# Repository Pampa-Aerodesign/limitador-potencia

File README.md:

# limitador-potencia

Sistema limitador de potência para motores BLDC com foco no projeto SAE Aerodesign 2024.

## Objetivo

Estamos utilizando um limitador de potência a fim de cumprir as restrições do regulamento.
Nosso GMP (conjunto motor/hélice/bateria) é capaz de consumir mais de 800 W de potência, então,
para maximizar o empuxo e a pontuação na competição, desenvolvemos este sistema.

## Como funciona

O sistema é composto por dois Arduinos Nano executando o mesmo código.
Os dois Arduinos vão fazer a leitura dos sensores de corrente e de tensão,
do sinal PWM vindo do ESC.

Após realizar as leituras, cada Arduino vai calcular um novo PWM para o motor levando em conta
a potência obtida dos sensores, de modo que a potência do motor não ultrapasse um determinado valor.

Cada Arduino também faz a leitura do PWM gerado pelo outro e verifica se o valor está dentro
de uma tolerância. Caso um dos Arduinos perceba que o PWM do outro Arduino está fora da tolerância,
seja por uma discrepância nos valores ou por uma falha no segundo Arduino,
um pino de verificação (Check) será levado ao nível lógico baixo, fazendo com que o PWM
dos Arduinos seja barrado e o PWM do receptor seja enviado ao ESC.

### Fluxograma

## Estrutura do repositório

- **limitador-potencia.ino** - Arquivo principal que inicializa o sistema;
- **params.hpp** - Arquivo que contém todas as configurações do sistema. Nele, são definidos os pinos, parâmetros, estruturas de dados e constantes;
- Pasta **src/** - Arquivos fonte contendo as funções utilizadas no arquivo principal;
- Pasta **inc/** - Arquivos cabeçalho contendo os protótipos das funções.

### Arquivos fonte

- **current.cpp** - funções relacionadas à leitura de corrente do motor;
- **voltage.cpp** - funções relacionadas à leitura de tensão da bateria;
- **pwm.cpp** - funções relacionadas à leitura dos sinais de PWM;

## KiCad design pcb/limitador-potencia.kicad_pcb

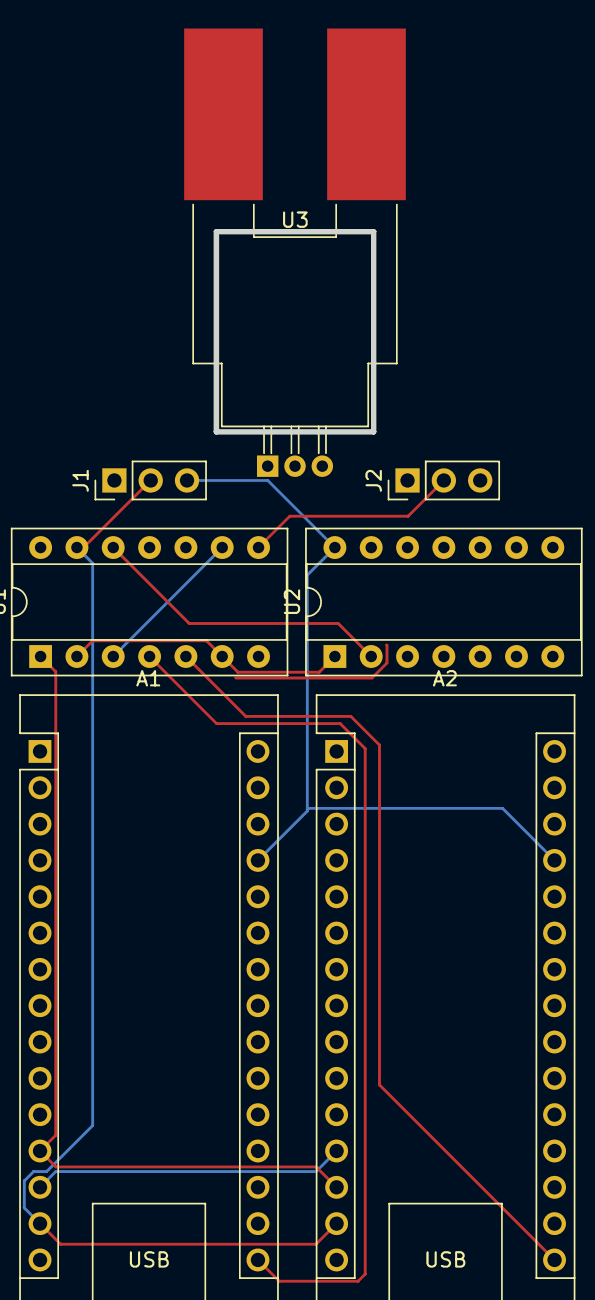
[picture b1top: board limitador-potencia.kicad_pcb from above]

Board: 2 copper layers, 7 parts (0 on the bottom side), 14 nets.

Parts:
A1, A2: Arduino_Nano_v2.x; Arduino_Nano
J1: RX Input; PinHeader_1x03_P2.54mm_Vertical
J2: ESC Output; PinHeader_1x03_P2.54mm_Vertical
U1: 74HC00; CERDIP-14_W7.62mm_SideBrazed_Socket
U2: 74AHC04; CERDIP-14_W7.62mm_SideBrazed_Socket
U3: ACS758xCB-100B-PSF; Allegro_CB_PSF

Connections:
+5V: A1.27 (+5V), A2.27 (+5V), J1.3, U1.14 (VCC), U2.14 (VCC), U3.1 (VCC)
GND: A1.4 (GND), A1.29 (GND), A2.4 (GND), A2.29 (GND), J1.1, J2.1, U1.7 (GND), U2.7 (GND), U3.2 (GND)
unnamed: A1.19 (A0), A2.19 (A0), U3.3 (VIOUT)
unnamed: A1.24 (A5), A2.24 (A5)
unnamed: A1.12 (D9), A2.13 (D10), U1.1
unnamed: A1.13 (D10), A2.12 (D9)
unnamed: A1.14 (D11), A2.14 (D11), J1.2, U1.13
unnamed: A1.16 (D13), U1.4
unnamed: A2.16 (D13), U1.5
unnamed: J2.2, U1.8
unnamed: U1.2, U1.6, U2.1
unnamed: U1.3, U1.9
unnamed: U1.10, U1.11
unnamed: U1.12, U2.2

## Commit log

2024-06-25 Código preliminar
2024-07-16 Renamed limitador.ino to limitador-potencia.ino Arduino requires the .ino file to have the same name as the parent folder Added .gitignore Moved things around to make more sense
2024-07-17 Added placeholder TODO functions
2024-07-19 Inclusion of PID controller for generate a new PWM output using PID Library from Arduino Community
2024-07-25 Removed input check pin
2024-07-25 Voltage measurement implemented
    UNTESTED
2024-07-25 Current measurement implemented
    UNTESTED
2024-07-25 Separated project into multiple files Created inc/ folder for header files Created src/ folder for source files Updated README.md
2024-07-25 Comments
2024-07-26 Added KiCad schematic Schematic and PCB are not complete
2024-07-26 Moved hardcoded ESC pin to params.hpp
2024-07-28 Using HEX 8S Power module Reading current and voltage sensor from the HEX 8S Power module for Pixhawk Implemented PID
    UNTESTED
2024-07-28 Added program flowchart
2024-07-30 Using interrupts to measure PWM width
2024-07-30 update docs
2024-07-30 Updated docs
2025-09-17 Update README.md
    Detalha o ano do projeto
